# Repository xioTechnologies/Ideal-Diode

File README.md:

Ideal-Diode
===========

An ideal diode circuit based on [Raspberry Pi B Power Protection Circuit](http://robotics.ong.id.au/2014/07/30/raspberry-pi-b-power-protection-circuit/).  The unpopulated PCB is available to [purchase from OSH Park](https://oshpark.com/shared_projects/qIJxjpxr) ($1.25 for 3 boards).

Photos
------

Schematic
---------

PCB Preview from OSH Park
-------------------------

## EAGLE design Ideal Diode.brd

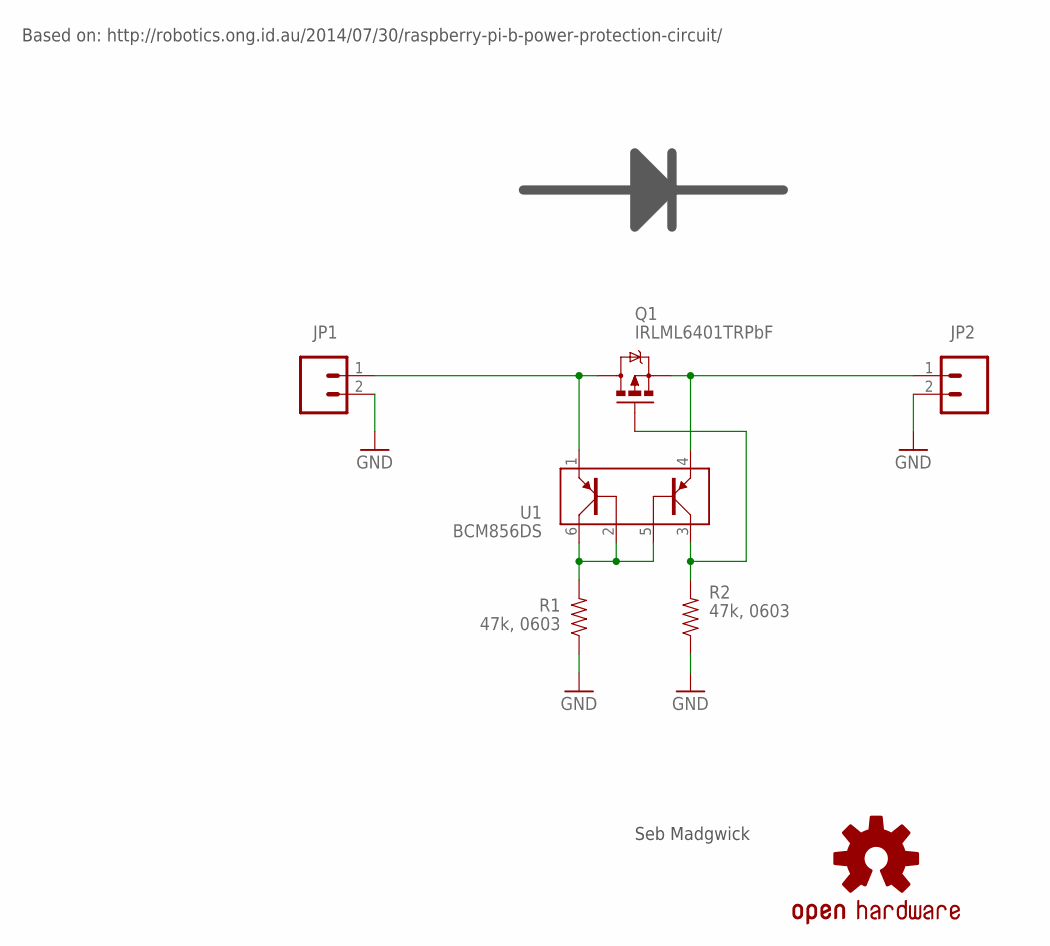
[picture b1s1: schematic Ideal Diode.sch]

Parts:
JP1, JP2: M02PTH3; 1X02_LONGPADS
LOGO1: OSHW-LOGOS; OSHW-LOGO-S
Q1: IRLML6401TRPbF; SOT23-3
R1, R2: 47k, 0603; 0603-RES
U1: BCM856DS; SOT457

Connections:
GND: JP1.2, JP2.2, R1.1, R2.1
unnamed: R1.2, U1.2, U1.5, U1.6
unnamed: Q1.1 (G), R2.2, U1.3
unnamed: JP2.1, Q1.2 (S), U1.4
unnamed: JP1.1, Q1.3 (D), U1.1

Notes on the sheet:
Based on: http://robotics.ong.id.au/2014/07/30/raspberry-pi-b-power-protection-circuit/
Seb Madgwick

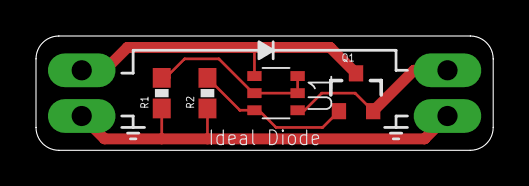
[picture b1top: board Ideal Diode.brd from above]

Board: 2 copper layers, 25.4 x 6.3 mm, 7 parts (1 on the bottom side), 5 nets.

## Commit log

2014-11-11 Commit project files
2014-11-11 Add schematic image
2014-12-18 Add photos

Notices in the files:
parts and their libraries:
SparkFun-Connectors: Licensing: Creative Commons ShareAlike 4.0 International - https://creativecommons.org/licenses/by-sa/4.0
